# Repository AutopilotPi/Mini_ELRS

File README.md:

# Mini_ELRS

The repo is a hardware design for ELRS(https://github.com/ExpressLRS/ExpressLRS) by Kicad 6.0. The design aim to construct a 
SMT module which could be integrated into PCB of Flight Controller or some other DIY projects easily. 

To lower the cost, there is cut area in the PCB. Because the half hole process in PCB sample production cost mucher higher, 
we can cut the extral area after the PCB production manually.

## License
Please notice that the license of this project is GPL 3.0. For hardware project, hope that you can share the changes if you make something different in the sch or pcb.

### reference
https://github.com/ExpressLRS/ExpressLRS-Hardware/tree/master/PCB/2400MHz/RX_Nano

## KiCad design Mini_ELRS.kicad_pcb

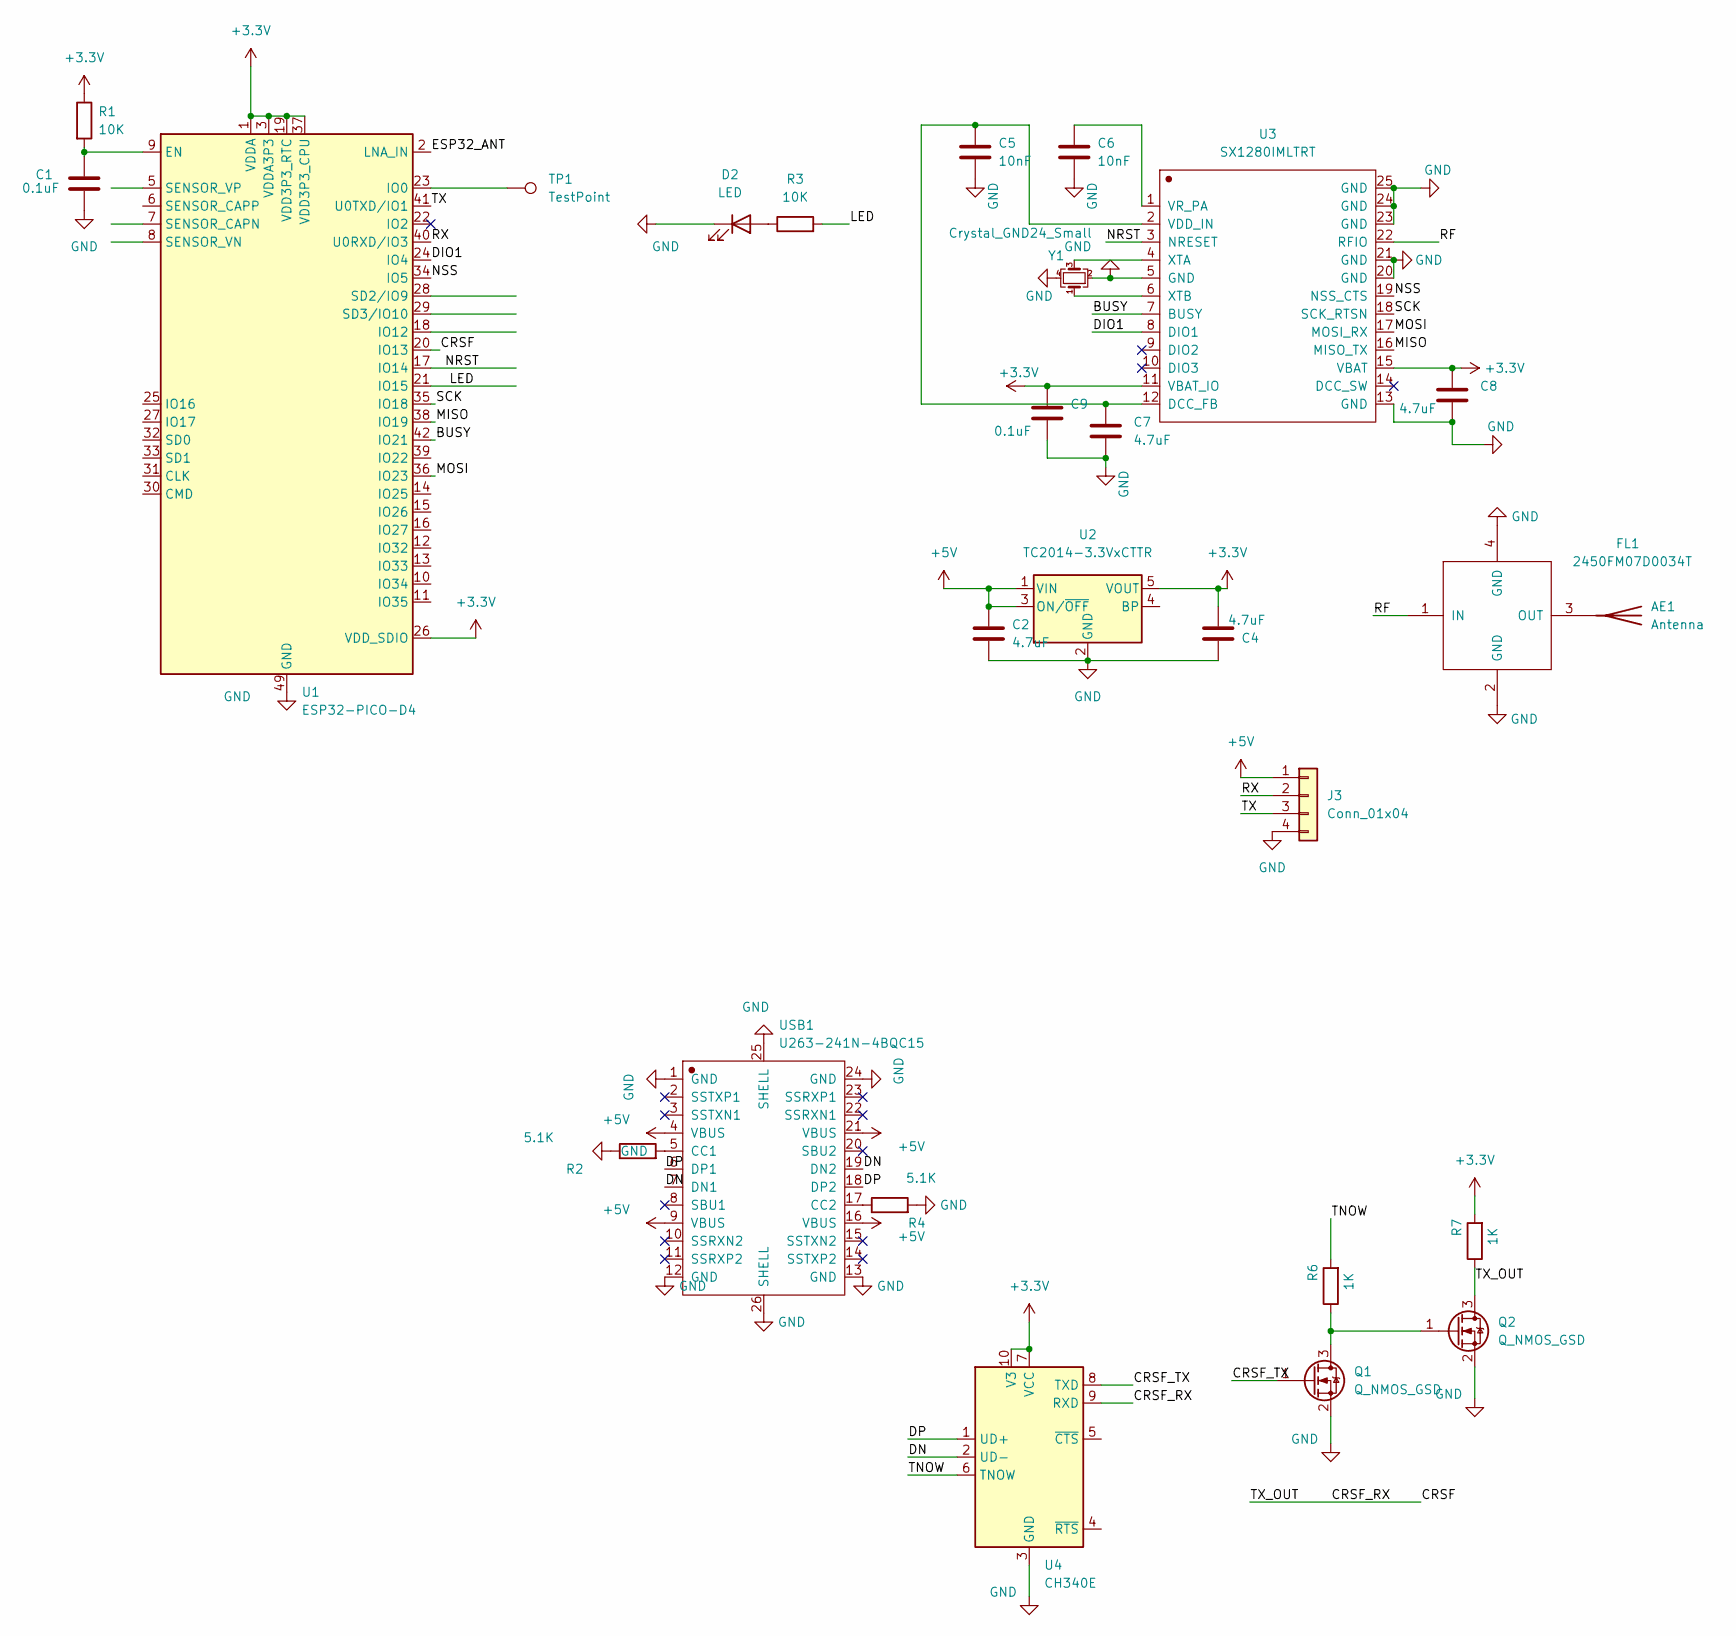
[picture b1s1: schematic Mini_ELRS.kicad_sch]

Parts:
AE1: Antenna; Johanson_2450AT43F0100
C1, C9: 0.1uF; C_0603_1608Metric
C2, C4, C7, C8: 4.7uF; C_0603_1608Metric
C5, C6: 10nF; C_0603_1608Metric
D2: LED; LED_0603_1608Metric
FL1: 2450FM07D0034T; FILTER-SMD_4P-L1.0-W0.5-L
J3: Conn_01x04; PinHeader_1x04_P2.54mm_Vertical
Q1, Q2: Q_NMOS_GSD; SOT-23
R1, R3: 10K; R_0603_1608Metric
R2, R4: 5.1K; R_0603_1608Metric
R6, R7: 1K; R_0603_1608Metric
TP1: TestPoint; TestPoint_THTPad_1.0x1.0mm_Drill0.5mm
U1: ESP32-PICO-D4; QFN-48-1EP_7x7mm_P0.5mm_EP5.3x5.3mm
U2: TC2014-3.3VxCTTR; SOT-23-5
U3: SX1280IMLTRT; QFN-24-1EP_4x4mm_P0.5mm_EP2.65x2.65mm
U4: CH340E; MSOP-10_3x3mm_P0.5mm
USB1: U263-241N-4BQC15; USB-C-SMD_U263-241N-4BQC15
Y1: Crystal_GND24_Small; Crystal_SMD_2520-4Pin_2.5x2.0mm

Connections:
+3V3: C4.1, C8.1, C9.1, R1.1, R7.2, U1.1 (VDDA), U1.3 (VDDA3P3), U1.4 (VDDA3P3), U1.19 (VDD3P3_RTC), U1.26 (VDD_SDIO), U1.37 (VDD3P3_CPU), U1.43 (VDDA), U1.46 (VDDA), U2.5 (VOUT), U3.11 (VBAT_IO), U3.15 (VBAT), U4.7 (VCC), U4.10 (V3)
+5V: C2.1, J3.1, U2.1 (VIN), U2.3 (ON/~OFF), USB1.4 (VBUS), USB1.9 (VBUS), USB1.16 (VBUS), USB1.21 (VBUS)
/BUSY: U1.42 (IO21), U3.7 (BUSY)
/CRSF: Q2.3 (D), R7.1, U1.20 (IO13), U4.9 (RXD)
/CRSF_TX: Q1.1 (G), U4.8 (TXD)
/DIO1: U1.24 (IO4), U3.8 (DIO1)
/DN: U4.2 (UD-), USB1.7 (DN1), USB1.19 (DN2)
/DP: U4.1 (UD+), USB1.6 (DP1), USB1.18 (DP2)
/ESP32_ANT: U1.2 (LNA_IN)
/LED: R3.2, U1.21 (IO15)
/MISO: U1.38 (IO19), U3.16 (MISO_TX)
/MOSI: U1.36 (IO23), U3.17 (MOSI_RX)
/NRST: U1.17 (IO14), U3.3 (NRESET)
/NSS: U1.34 (IO5), U3.19 (NSS_CTS)
/RF: FL1.1 (IN), U3.22 (RFIO)
/RX: J3.2, U1.40 (U0RXD/IO3)
/SCK: U1.35 (IO18), U3.18 (SCK_RTSN)
/TNOW: R6.2, U4.6 (TNOW)
/TX: J3.3, U1.41 (U0TXD/IO1)
GND: C1.2, C2.2, C4.2, C5.2, C6.2, C7.2, C8.2, C9.2, D2.1 (K), FL1.2 (GND), FL1.4 (GND), J3.4, Q1.2 (S), Q2.2 (S), R2.1, R4.2, U1.49 (GND), U2.2 (GND), U3.5 (GND), U3.13 (GND), U3.20 (GND), U3.21 (GND), U3.23 (GND), U3.24 (GND), U3.25 (GND), U4.3 (GND), USB1.1 (GND), USB1.12 (GND), USB1.13 (GND), USB1.24 (GND), USB1.25 (SHELL), USB1.26 (SHELL), Y1.2, Y1.4
unnamed: AE1.1 (A), FL1.3 (OUT)
unnamed: C1.1, R1.2, U1.9 (EN)
unnamed: C5.1, C7.1, U3.2 (VDD_IN), U3.12 (DCC_FB)
unnamed: C6.1, U3.1 (VR_PA)
unnamed: D2.2 (A), R3.1
unnamed: Q1.3 (D), Q2.1 (G), R6.1
unnamed: R2.2, USB1.5 (CC1)
unnamed: R4.1, USB1.17 (CC2)
unnamed: TP1.1, U1.23 (IO0)
unnamed: U3.4 (XTA), Y1.3
unnamed: U3.6 (XTB), Y1.1

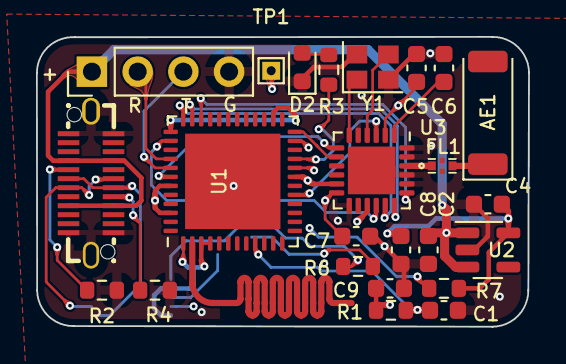
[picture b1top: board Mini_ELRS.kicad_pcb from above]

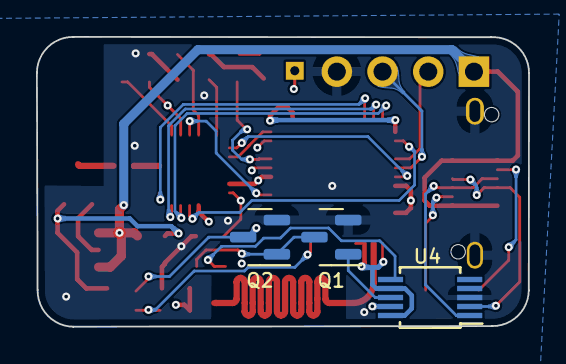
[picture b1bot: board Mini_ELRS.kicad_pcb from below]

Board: 4 copper layers, 27.3 x 16.1 mm, 27 parts (3 on the bottom side), 30 nets.

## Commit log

2022-04-02 init
2022-04-04 remove the copper in the cutting area, which would cause the lack of connection after cutting
2022-04-05 add images
2022-04-05 add docs
2022-05-25 stash for esp8266
2022-05-25 v0.9 test
2022-08-21 update esp32_with_mos
2022-08-21 fix the 2.54 connector package.
2022-09-06 swap some pwm pins net name
2022-09-17 remove some unnecessary cap/res, remove ipex4.0 , add esp8266 lna
2022-09-20 remove something unncessary
2022-09-21 finished TX mobile
2022-09-30 change some value of res
2022-09-30 finished pcb. using normal layer stack
2022-10-26 use another Type-c package
2022-11-25 add pin.json
2022-12-25 edit the value of pulldown res of IO5
